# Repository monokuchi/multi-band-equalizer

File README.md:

<!-- PROJECT LOGO -->
<div align="center">
  <h1>Multi-Band Equalizer</h1>
  <p>
    Multi-band parametric equalizer implemented using a STM32H7 ARM7 Microcontroller along with a Cirrus Logic CS4272-CZZ Audio Codec
  </p>
</div>

<!-- PROJECT DESCRIPTION -->
<h2>Description</h2> 

<header>
    <ul>
        <li><h3>Multi-Band-Equalizer Front Side</h3></li>
    </ul>
</header>

![Multi-Band-Equalizer PCB Front Side][multi-band-equalizer-pcb-front]

<header>
    <ul>
        <li><h3>Multi-Band-Equalizer Back Side</h3></li>
    </ul>
</header>

![Multi-Band-Equalizer PCB Back Side][multi-band-equalizer-pcb-back]

<header>
    <ul>
        <li><h3>CS4272-CZZ Breakout Board</h3></li>
    </ul>
</header>

![CS4272-CZZ_Breakout_Board PCB Front Side][cs4272-czz_breakout_board-front]

10-band parametric equalizer using digital 2 stage IIR peaking filters.

Features:
* Efficent pipelining of stereo audio samples to/from the MCU and the codec by utilizing double buffering as well as DMA streams
* Fast computation of cascaded IIR filter stages by taking advantage of ARM's CMSIS DSP libaries (Decreases compute time by ~64%!)
* Generic design of hardware allows for this PCB to used for more then an EQ. All you need to do is change the firmware to alter the processing of the audio samples

Check out this *[script][python-script-url]* for simulating the cascaded filter responses

<p align="right">(<a href="#readme-top">back to top</a>)</p>

<!-- MARKDOWN LINKS & IMAGES -->
[multi-band-equalizer-pcb-front]: pcb/multi-band-equalizer/References/multi-band-equalizer_front.png
[multi-band-equalizer-pcb-back]: pcb/multi-band-equalizer/References/multi-band-equalizer_back.png
[cs4272-czz_breakout_board-front]: pcb/CS4272-CZZ_Breakout_Board/References/CS4272-CZZ_Breakout_Board.png
[python-script-url]: scripts/peaking_filter.py

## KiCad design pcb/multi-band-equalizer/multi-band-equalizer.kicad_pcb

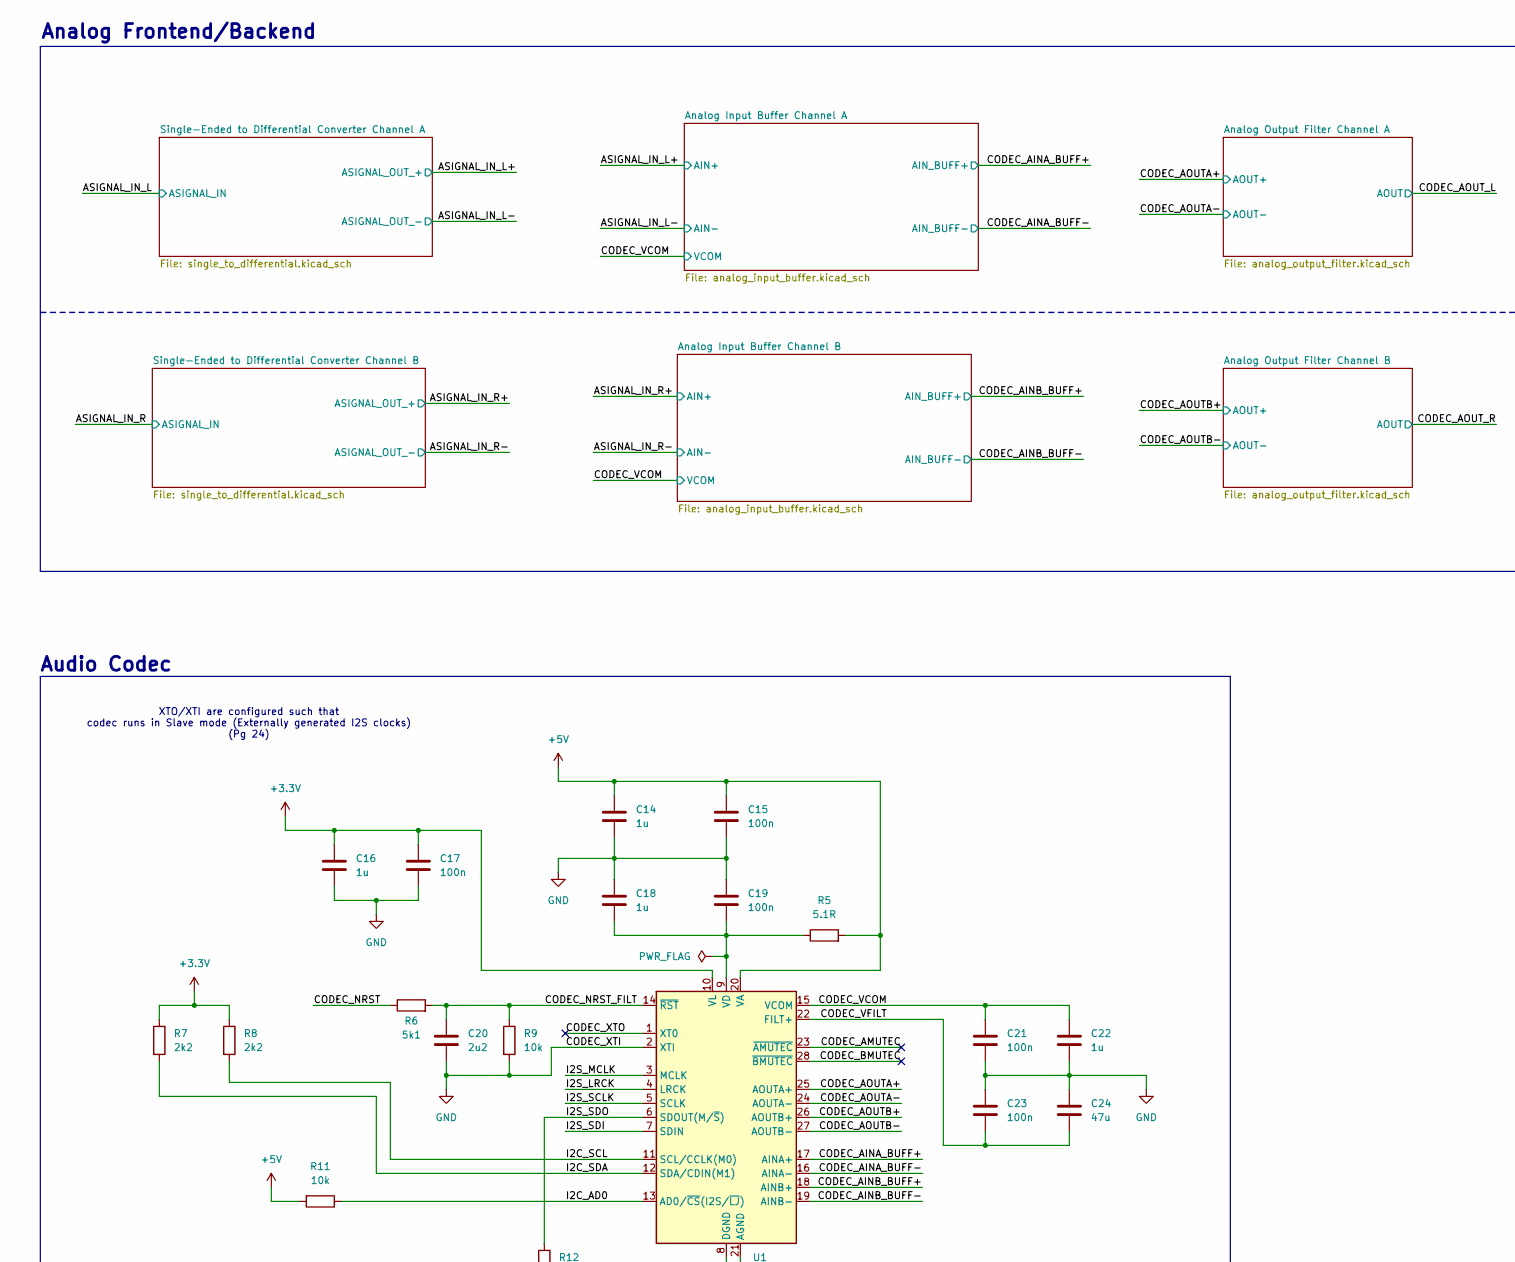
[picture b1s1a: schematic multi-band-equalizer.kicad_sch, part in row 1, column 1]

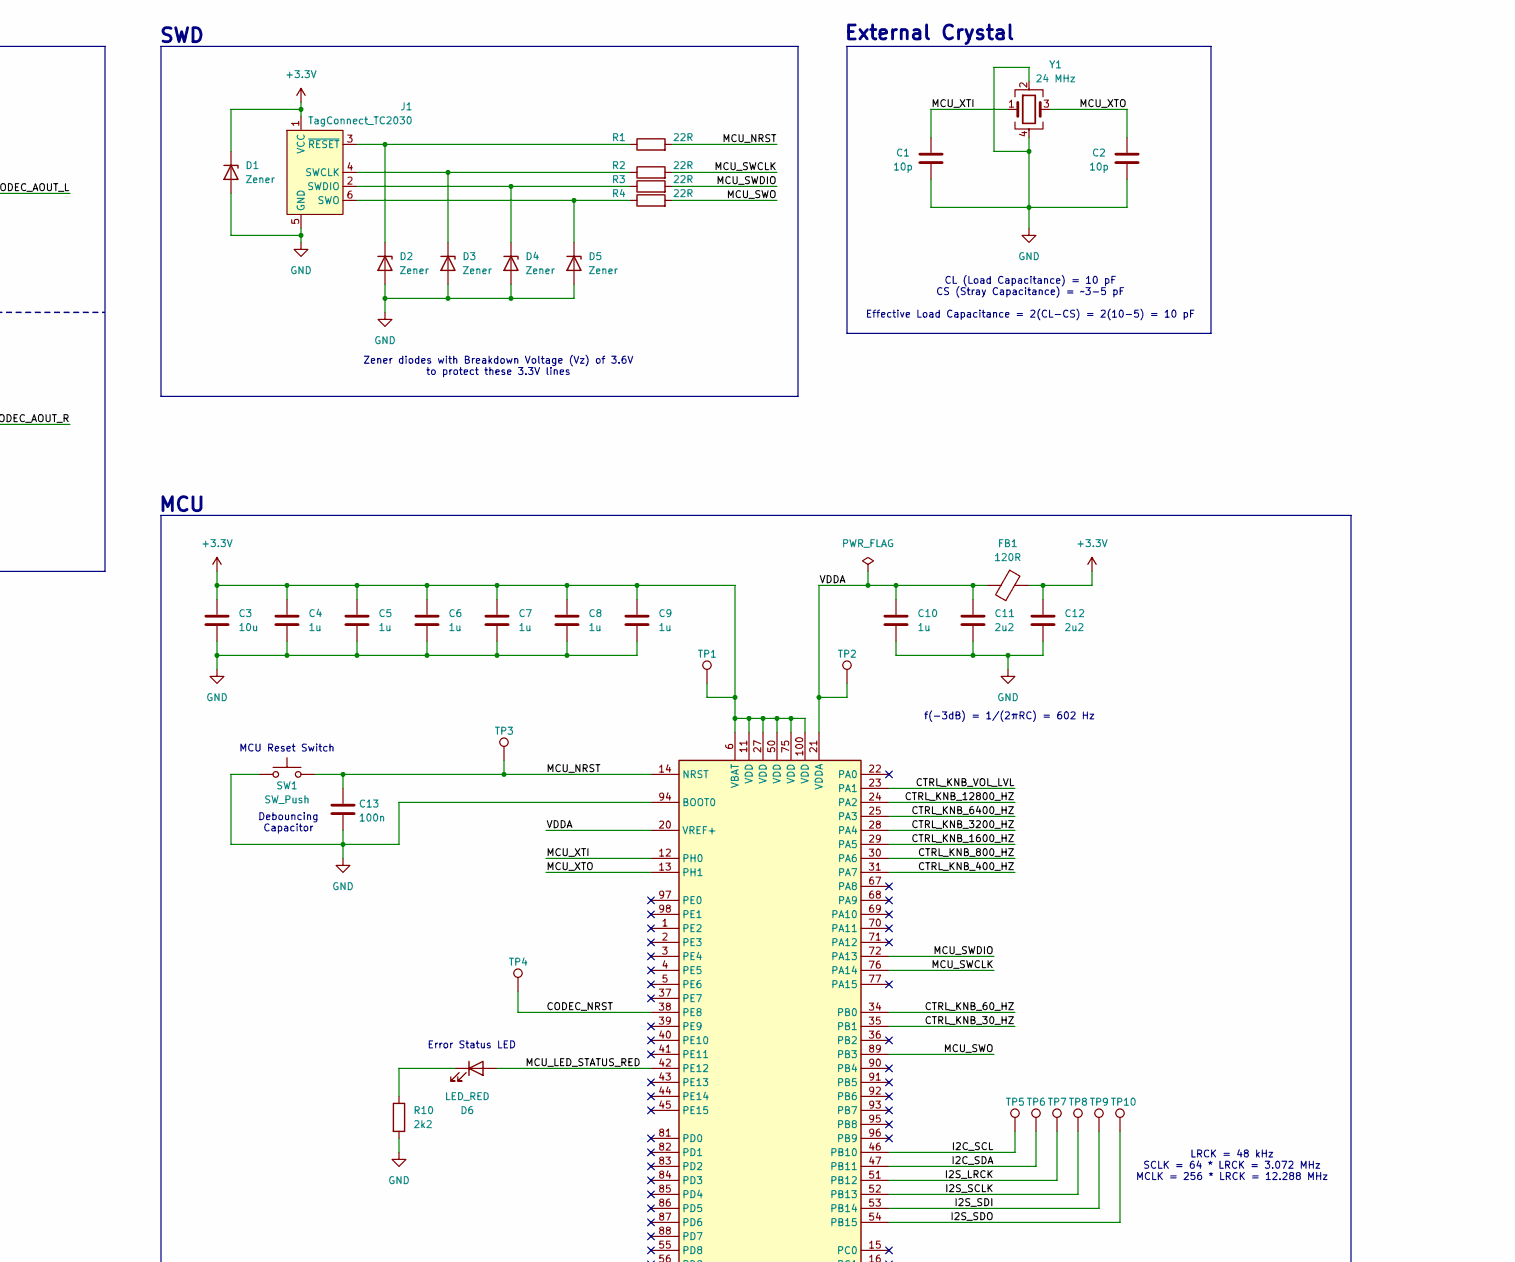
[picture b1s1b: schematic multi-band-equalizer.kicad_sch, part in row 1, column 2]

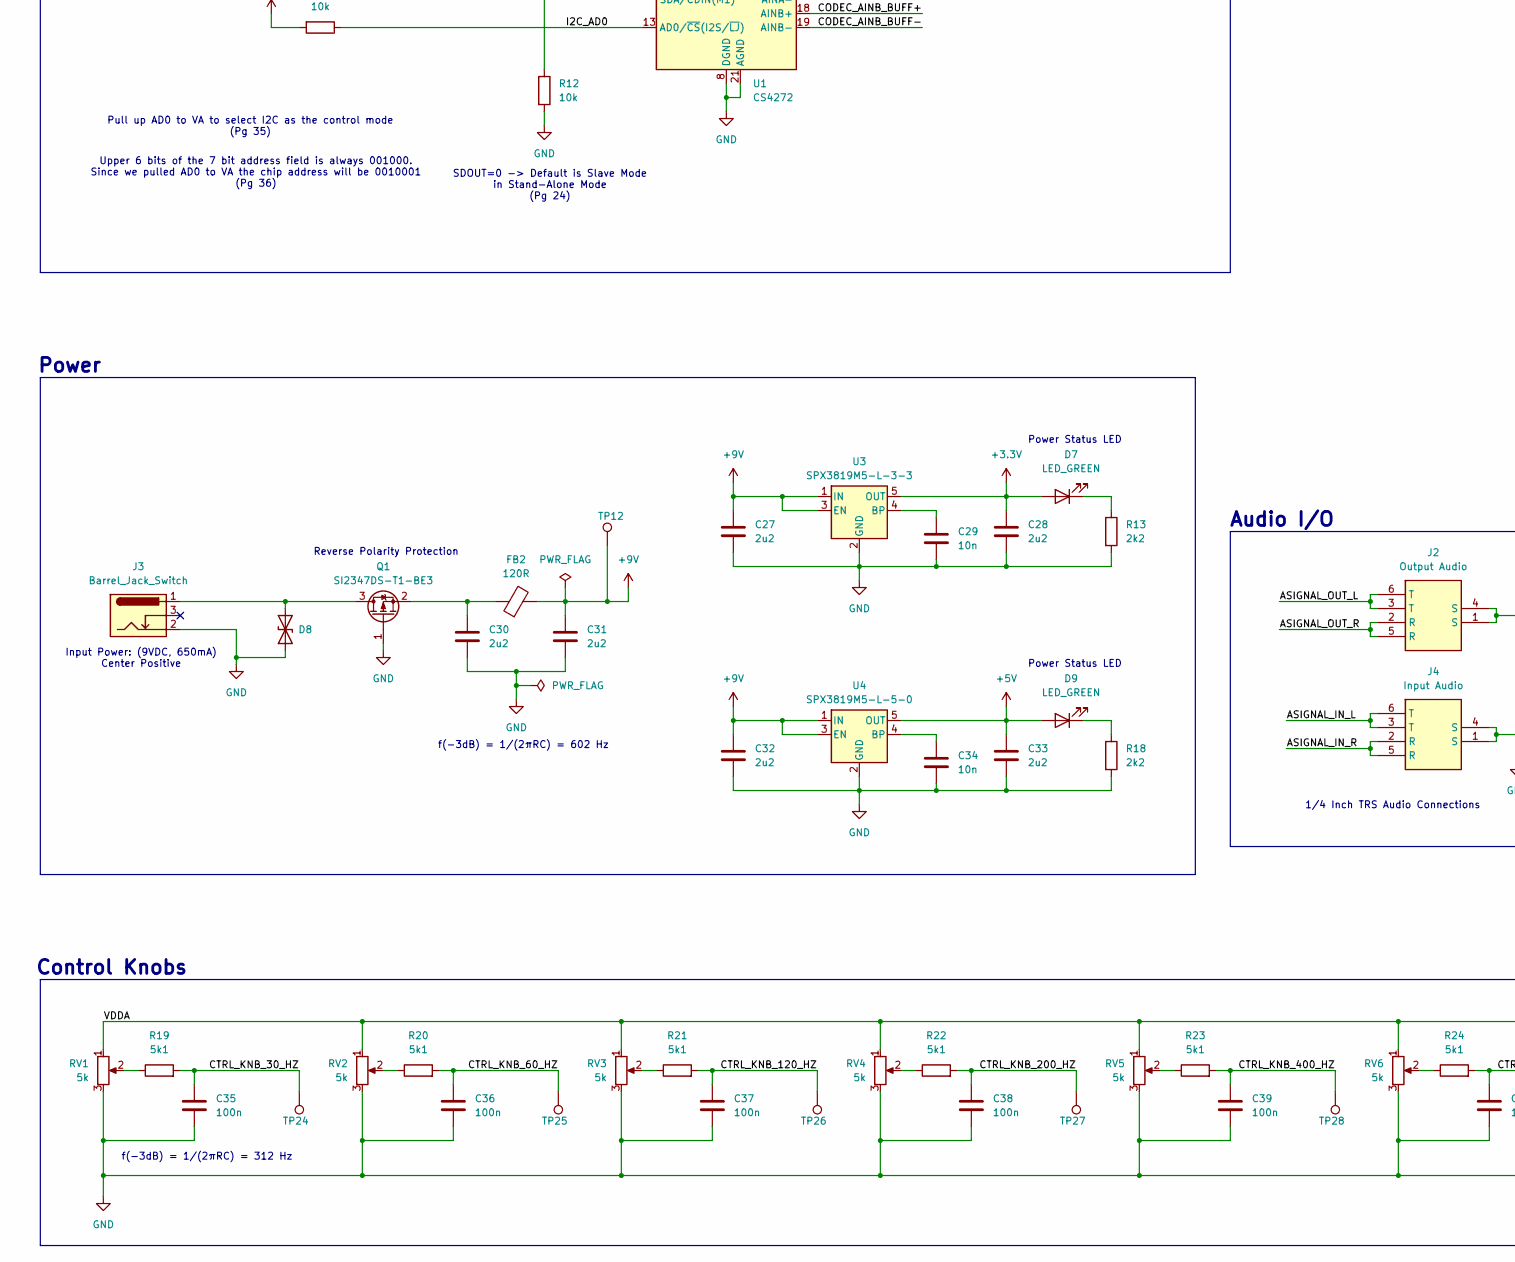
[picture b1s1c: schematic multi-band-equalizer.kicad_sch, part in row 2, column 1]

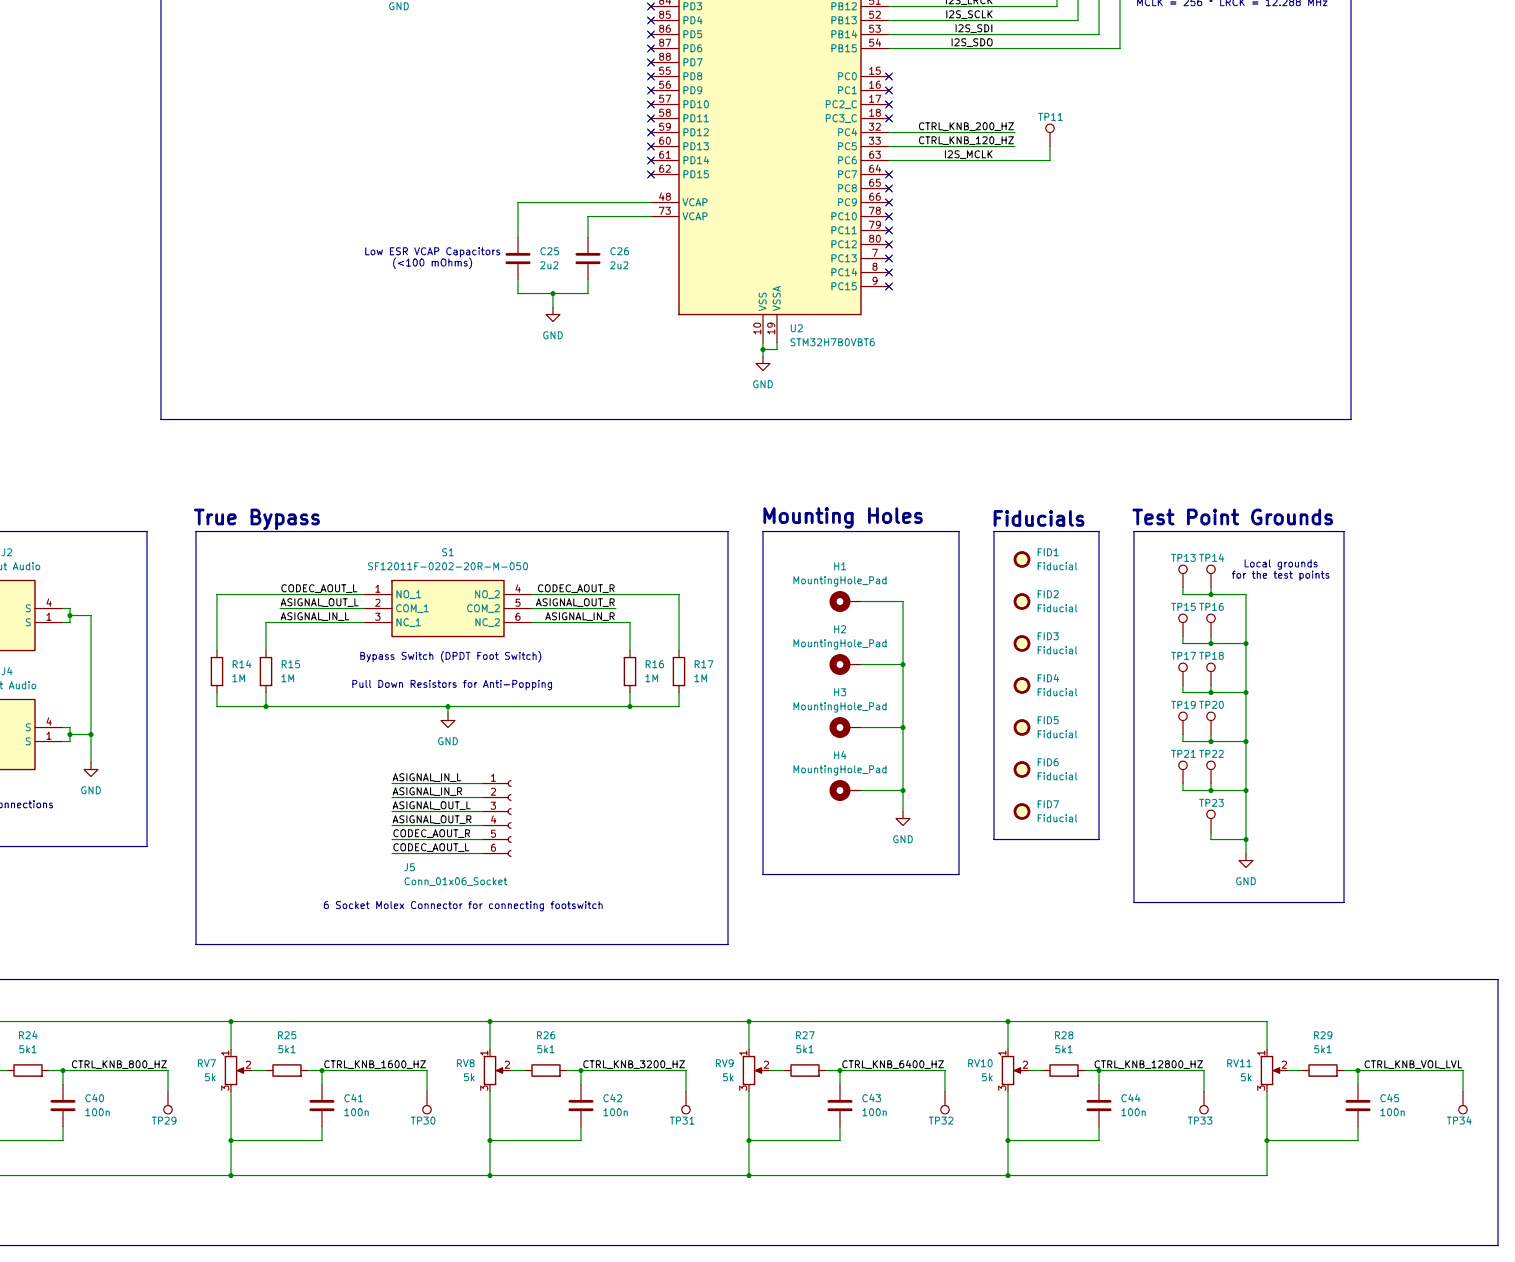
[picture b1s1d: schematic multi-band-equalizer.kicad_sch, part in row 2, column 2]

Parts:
C1, C2: 10p; C_0805_2012Metric
C3: 10u; C_0805_2012Metric
C4, C5, C6, C7, C8, C9, C10, C14, C16, C18, C22: 1u; C_0805_2012Metric
C11, C12, C20, C25, C26, C27, C28, C30, C31, C32, C33: 2u2; C_0805_2012Metric
C13, C15, C17, C19, C21, C23, C35, C36, C37, C38, C39, C40, C41, C42, C43, C44, C45: 100n; C_0805_2012Metric
C24: 47u; C_0805_2012Metric
C29, C34: 10n; C_0805_2012Metric
D1, D2, D3, D4, D5: Zener; D_SOD-323
D6: LED_RED; LED_0805_2012Metric
D7, D9: LED_GREEN; LED_0805_2012Metric
D8: D_TVS; D_SOD-123F
FB1, FB2: 120R; L_0805_2012Metric
FID1, FID2, FID3, FID4, FID5, FID6: Fiducial; Fiducial_1mm_Mask3mm
FID7: Fiducial; Fiducial_1mm_Mask2mm
H1, H2, H3, H4: MountingHole_Pad; MountingHole_4.3mm_M4_Pad_Via
J1: TagConnect_TC2030; Tag-Connect_TC2030-IDC-FP_2x03_P1.27mm_Vertical
J2: Output Audio; ACJSMHDR; Manufacturer_Part_Number ACJS-MHDR; Mouser Part Number 523-ACJS-MHDR
J3: Barrel_Jack_Switch; BarrelJack_Horizontal
J4: Input Audio; ACJSMHDR; Manufacturer_Part_Number ACJS-MHDR; Mouser Part Number 523-ACJS-MHDR
J5: Conn_01x06_Socket; JST_XH_S6B-XH-A_1x06_P2.50mm_Horizontal
Q1: SI2347DS-T1-BE3; SOT-23-3
R1, R2, R3, R4: 22R; R_0805_2012Metric
R5: 5.1R; R_0805_2012Metric
R6, R19, R20, R21, R22, R23, R24, R25, R26, R27, R28, R29: 5k1; R_0805_2012Metric
R7, R8, R10, R13, R18: 2k2; R_0805_2012Metric
R9, R11, R12: 10k; R_0805_2012Metric
R14, R15, R16, R17: 1M; R_0805_2012Metric
RV1, RV2, RV3, RV4, RV5, RV6, RV7, RV8, RV9, RV10, RV11: 5k; PTA2043-2015CPB502
S1: SF12011F-0202-20R-M-050; SF12011F020220RM050; Manufacturer_Part_Number SF12011F-0202-20R-M-050; Mouser Part Number 107-SF12011F-M
SW1: SW_Push; SW_PUSH_6mm_H4.3mm
TP1, TP2, TP3, TP4, TP5, TP6, TP7, TP8, TP9, TP10, TP11, TP12, TP13, TP14, TP15, TP16, TP17, TP18, TP19, TP20, TP21, TP22, TP23, TP24, TP25, TP26, TP27, TP28, TP29, TP30, TP31, TP32, TP33, TP34: TestPoint; TestPoint_THTPad_D1.0mm_Drill0.5mm
U1: CS4272; TSSOP-28_4.4x9.7mm_P0.65mm
U2: STM32H7B0VBT6; LQFP-100_14x14mm_P0.5mm
U3: SPX3819M5-L-3-3; SOT-23-5
U4: SPX3819M5-L-5-0; SOT-23-5
Y1: 24 MHz; Crystal_SMD_2520-4Pin_2.5x2.0mm

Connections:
+3.3V: C3.1, C4.1, C5.1, C6.1, C7.1, C8.1, C9.1, C12.1, C16.1, C17.1, C28.1, D1.1 (K), D7.2 (A), FB1.2, J1.1 (VCC), R7.1, R8.1, TP1.1, U1.10 (VL), U2.6 (VBAT), U2.11 (VDD), U2.27 (VDD), U2.50 (VDD), U2.75 (VDD), U2.100 (VDD), U3.5 (OUT)
+5V: C14.1, C15.1, C33.1, D9.2 (A), R5.2, R11.2, U1.20 (VA), U4.5 (OUT); also elsewhere on the board
+9V: C27.1, C31.1, C32.1, FB2.2, TP12.1, U3.1 (IN), U3.3 (EN), U4.1 (IN), U4.3 (EN)
/ASIGNAL_IN_L: J4.3 (T), J4.6 (T), J5.1, R15.1, S1.3 (NC_1); also elsewhere on the board
/ASIGNAL_IN_R: J4.2 (R), J4.5 (R), J5.2, R16.1, S1.6 (NC_2); also elsewhere on the board
/ASIGNAL_OUT_L: J2.3 (T), J2.6 (T), J5.3, S1.2 (COM_1)
/ASIGNAL_OUT_R: J2.2 (R), J2.5 (R), J5.4, S1.5 (COM_2)
/CODEC_AINA_BUFF+: U1.17 (AINA+); also elsewhere on the board
/CODEC_AINA_BUFF-: U1.16 (AINA-); also elsewhere on the board
/CODEC_AINB_BUFF+: U1.18 (AINB+); also elsewhere on the board
/CODEC_AINB_BUFF-: U1.19 (AINB-); also elsewhere on the board
/CODEC_AMUTEC: U1.23 (~AMUTEC)
/CODEC_AOUTA+: U1.25 (AOUTA+); also elsewhere on the board
/CODEC_AOUTA-: U1.24 (AOUTA-); also elsewhere on the board
/CODEC_AOUTB+: U1.26 (AOUTB+); also elsewhere on the board
/CODEC_AOUTB-: U1.27 (AOUTB-); also elsewhere on the board
/CODEC_AOUT_L: J5.6, R14.1, S1.1 (NO_1); also elsewhere on the board
/CODEC_AOUT_R: J5.5, R17.1, S1.4 (NO_2); also elsewhere on the board
/CODEC_BMUTEC: U1.28 (~BMUTEC)
/CODEC_NRST: R6.1, TP4.1, U2.38 (PE8)
/CODEC_NRST_FILT: C20.1, R6.2, R9.1, U1.14 (~RST)
/CODEC_VCOM: C21.1, C22.1, U1.15 (VCOM); also elsewhere on the board
/CODEC_VFILT: C23.2, C24.2, U1.22 (FILT+)
/CODEC_XTO: U1.1 (XT0)
/CTRL_KNB_30_HZ: C35.1, R19.2, TP24.1, U2.35 (PB1)
/CTRL_KNB_60_HZ: C36.1, R20.2, TP25.1, U2.34 (PB0)
/CTRL_KNB_120_HZ: C37.1, R21.2, TP26.1, U2.33 (PC5)
/CTRL_KNB_200_HZ: C38.1, R22.2, TP27.1, U2.32 (PC4)
/CTRL_KNB_400_HZ: C39.1, R23.2, TP28.1, U2.31 (PA7)
/CTRL_KNB_800_HZ: C40.1, R24.2, TP29.1, U2.30 (PA6)
/CTRL_KNB_1600_HZ: C41.1, R25.2, TP30.1, U2.29 (PA5)
/CTRL_KNB_3200_HZ: C42.1, R26.2, TP31.1, U2.28 (PA4)
/CTRL_KNB_6400_HZ: C43.1, R27.2, TP32.1, U2.25 (PA3)
/CTRL_KNB_12800_HZ: C44.1, R28.2, TP33.1, U2.24 (PA2)
/CTRL_KNB_VOL_LVL: C45.1, R29.2, TP34.1, U2.23 (PA1)
/I2C_AD0: R11.1, U1.13 (AD0/~CS(I2S/~LJ))
/I2C_SCL: R8.2, TP5.1, U1.11 (SCL/CCLK(M0)), U2.46 (PB10)
/I2C_SDA: R7.2, TP6.1, U1.12 (SDA/CDIN(M1)), U2.47 (PB11)
/I2S_LRCK: TP7.1, U1.4 (LRCK), U2.51 (PB12)
/I2S_MCLK: TP11.1, U1.3 (MCLK), U2.63 (PC6)
/I2S_SCLK: TP8.1, U1.5 (SCLK), U2.52 (PB13)
/I2S_SDI: TP9.1, U1.7 (SDIN), U2.53 (PB14)
/I2S_SDO: R12.1, TP10.1, U1.6 (SDOUT(M/~S)), U2.54 (PB15)
/MCU_LED_STATUS_RED: D6.2 (A), U2.42 (PE12)
/MCU_NRST: C13.1, R1.2, SW1.2, TP3.1, U2.14 (NRST)
/MCU_SWCLK: R2.2, U2.76 (PA14)
/MCU_SWDIO: R3.2, U2.72 (PA13)
/MCU_SWO: R4.2, U2.89 (PB3)
/MCU_XTI: C1.1, U2.12 (PH0), Y1.1
/MCU_XTO: C2.1, U2.13 (PH1), Y1.3
/VDDA: C10.1, C11.1, FB1.1, RV1.1, RV2.1, RV3.1, RV4.1, RV5.1, RV6.1, RV7.1, RV8.1, RV9.1, RV10.1, RV11.1, TP2.1, U2.20 (VREF+), U2.21 (VDDA)
GND: C1.2, C2.2, C3.2, C4.2, C5.2, C6.2, C7.2, C8.2, C9.2, C10.2, C11.2, C12.2, C13.2, C14.2, C15.2, C16.2, C17.2, C18.1, C19.1, C20.2, C21.2, C22.2, C23.1, C24.1, C25.2, C26.2, C27.2, C28.2, C29.2, C30.2, C31.2, C32.2, C33.2, C34.2, C35.2, C36.2, C37.2, C38.2, C39.2, C40.2, C41.2, C42.2, C43.2, C44.2, C45.2, D1.2 (A), D2.2 (A), D3.2 (A), D4.2 (A), D5.2 (A), D8.1 (A1), H1.1, H2.1, H3.1, H4.1, J1.5 (GND), J2.1 (S), J2.4 (S), J3.2, J4.1 (S), J4.4 (S), Q1.1 (G), R9.2, R10.2, R12.2, R13.2, R14.2, R15.2, R16.2, R17.2, R18.2, RV1.3, RV2.3, RV3.3, RV4.3, RV5.3, RV6.3, RV7.3, RV8.3, RV9.3, RV10.3, RV11.3, SW1.1, TP13.1, TP14.1, TP15.1, TP16.1, TP17.1, TP18.1, TP19.1, TP20.1, TP21.1, TP22.1, TP23.1, U1.2 (XTI), U1.8 (DGND), U1.21 (AGND), U2.10 (VSS), U2.19 (VSSA), U2.26 (VSS), U2.49 (VSS), U2.74 (VSS), U2.94 (BOOT0), U2.99 (VSS), U3.2 (GND), U4.2 (GND), Y1.2, Y1.4; also elsewhere on the board
unnamed: C25.1, U2.48 (VCAP)
unnamed: C26.1, U2.73 (VCAP)
unnamed: D2.1 (K), J1.3 (~RESET), R1.1
unnamed: D3.1 (K), J1.4 (SWCLK), R2.1
unnamed: D4.1 (K), J1.2 (SWDIO), R3.1
unnamed: D5.1 (K), J1.6 (SWO), R4.1
unnamed: D6.1 (K), R10.1
unnamed: D7.1 (K), R13.1
unnamed: D8.2 (A2), J3.1, Q1.3 (D)
unnamed: D9.1 (K), R18.1
unnamed: C30.1, FB2.1, Q1.2 (S)
unnamed: R19.1, RV1.2
unnamed: R20.1, RV2.2
unnamed: R21.1, RV3.2
unnamed: R22.1, RV4.2
unnamed: R23.1, RV5.2
unnamed: R24.1, RV6.2
unnamed: R25.1, RV7.2
unnamed: R26.1, RV8.2
unnamed: R27.1, RV9.2
unnamed: R28.1, RV10.2
unnamed: R29.1, RV11.2
unnamed: C18.2, C19.2, R5.1, U1.9 (VD)
unnamed: C29.1, U3.4 (BP)
unnamed: C34.1, U4.4 (BP)

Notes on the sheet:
Power Status LED
Test Point Grounds
1/4 Inch TRS Audio Connections
Debouncing Capacitor
Bypass Switch (DPDT Foot Switch)
Reverse Polarity Protection
Audio I/O
Error Status LED
Upper 6 bits of the 7 bit address field is always 001000. Since we pulled AD0 to VA the chip address will be 0010001 (Pg 36)
XTO/XTI are configured such that codec runs in Slave mode (Externally generated I2S clocks) (Pg 24)
f(-3dB) = 1/(2πRC) = 602 Hz
MCU
f(-3dB) = 1/(2πRC) = 312 Hz
SWD
LRCK = 48 kHz SCLK = 64 * LRCK = 3.072 MHz MCLK = 256 * LRCK = 12.288 MHz
6 Socket Molex Connector for connecting footswitch
Audio Codec
Local grounds for the test points
Low ESR VCAP Capacitors (<100 mOhms)
Zener diodes with Breakdown Voltage (Vz) of 3.6V to protect these 3.3V lines
SDOUT=0 -> Default is Slave Mode in Stand-Alone Mode (Pg 24)
Fiducials
True Bypass
External Crystal
CL (Load Capacitance) = 10 pF CS (Stray Capacitance) = ~3-5 pF Effective Load Capacitance = 2(CL-CS) = 2(10-5) = 10 pF
Power
Pull Down Resistors for Anti-Popping
Analog Frontend/Backend
Control Knobs
Input Power: (9VDC, 650mA) Center Positive
Mounting Holes
MCU Reset Switch
Pull up AD0 to VA to select I2C as the control mode (Pg 35)

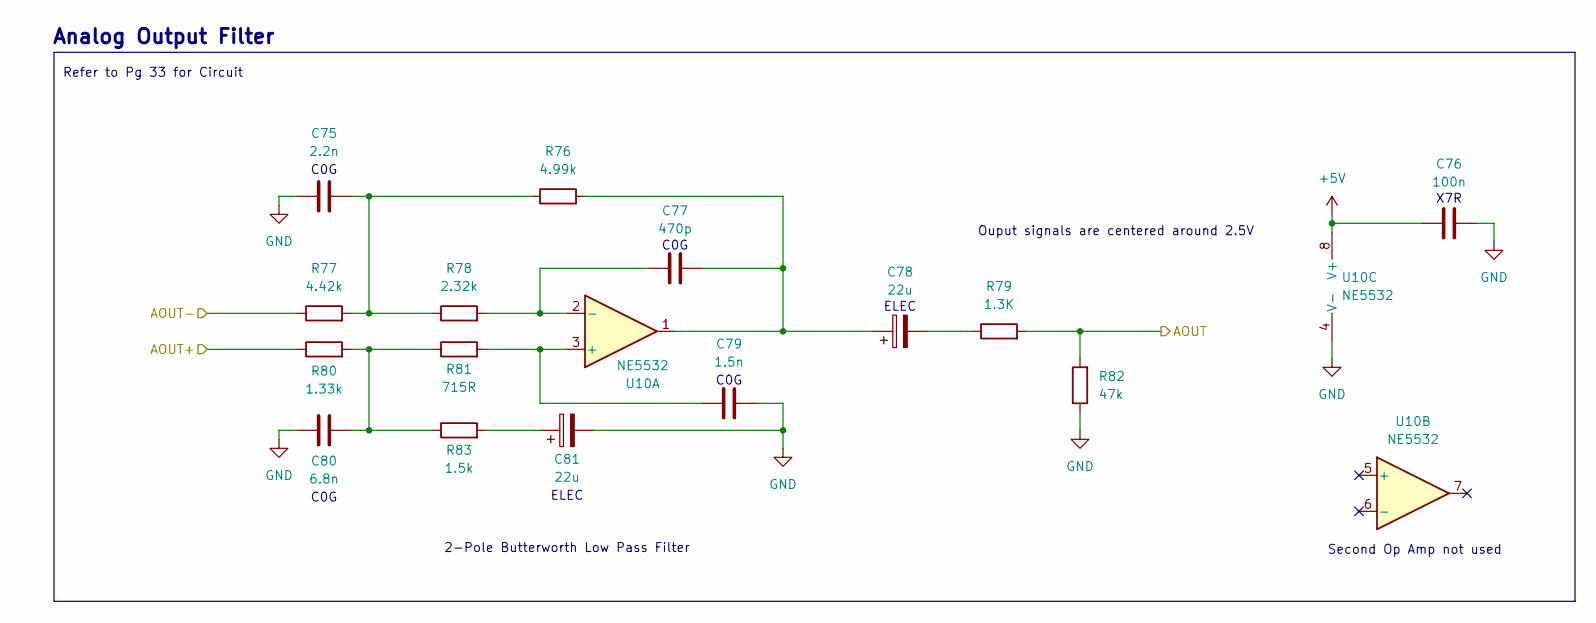
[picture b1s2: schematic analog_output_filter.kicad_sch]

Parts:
C75: 2.2n; C_0805_2012Metric
C76: 100n; C_0805_2012Metric
C77: 470p; C_0805_2012Metric
C78, C81: 22u; CP_Elec_4x5.4
C79: 1.5n; C_0805_2012Metric
C80: 6.8n; C_0805_2012Metric
R76: 4.99k; R_0805_2012Metric
R77: 4.42k; R_0805_2012Metric
R78: 2.32k; R_0805_2012Metric
R79: 1.3K; R_0805_2012Metric
R80: 1.33k; R_0805_2012Metric
R81: 715R; R_0805_2012Metric
R82: 47k; R_0805_2012Metric
R83: 1.5k; R_0805_2012Metric
U10: NE5532; SOIC-8_3.9x4.9mm_P1.27mm

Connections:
+5V: C76.1, U10.8 (V+); also elsewhere on the board
/CODEC_AOUTB+: R80.1; also elsewhere on the board
/CODEC_AOUTB-: R77.1; also elsewhere on the board
/CODEC_AOUT_R: R79.2, R82.2; also elsewhere on the board
GND: C75.1, C76.2, C79.2, C80.1, C81.2, R82.1, U10.4 (V-); also elsewhere on the board
unnamed: C75.2, R76.1, R77.2, R78.1
unnamed: C77.2, C78.1, R76.2, U10.1
unnamed: C78.2, R79.1
unnamed: C80.2, R80.2, R81.1, R83.1
unnamed: C81.1, R83.2
unnamed: C79.1, R81.2, U10.3 (+)
unnamed: C77.1, R78.2, U10.2 (-)

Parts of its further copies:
C68: 2.2n; C_0805_2012Metric
C69: 100n; C_0805_2012Metric
C70: 470p; C_0805_2012Metric
C71, C74: 22u; CP_Elec_4x5.4
C72: 1.5n; C_0805_2012Metric
C73: 6.8n; C_0805_2012Metric
R68: 4.99k; R_0805_2012Metric
R69: 4.42k; R_0805_2012Metric
R70: 2.32k; R_0805_2012Metric
R71: 1.3K; R_0805_2012Metric
R72: 1.33k; R_0805_2012Metric
R73: 715R; R_0805_2012Metric
R74: 47k; R_0805_2012Metric
R75: 1.5k; R_0805_2012Metric
U9: NE5532; SOIC-8_3.9x4.9mm_P1.27mm

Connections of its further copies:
+5V: C69.1, U9.8 (V+); also elsewhere on the board
/CODEC_AOUTA+: R72.1; also elsewhere on the board
/CODEC_AOUTA-: R69.1; also elsewhere on the board
/CODEC_AOUT_L: R71.2, R74.2; also elsewhere on the board
GND: C68.1, C69.2, C72.2, C73.1, C74.2, R74.1, U9.4 (V-); also elsewhere on the board
unnamed: C68.2, R68.1, R69.2, R70.1
unnamed: C70.2, C71.1, R68.2, U9.1
unnamed: C71.2, R71.1
unnamed: C73.2, R72.2, R73.1, R75.1
unnamed: C74.1, R75.2
unnamed: C72.1, R73.2, U9.3 (+)
unnamed: C70.1, R70.2, U9.2 (-)

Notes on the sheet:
C0G
Refer to Pg 33 for Circuit
X7R
2-Pole Butterworth Low Pass Filter
Second Op Amp not used
Ouput signals are centered around 2.5V
ELEC
Analog Output Filter

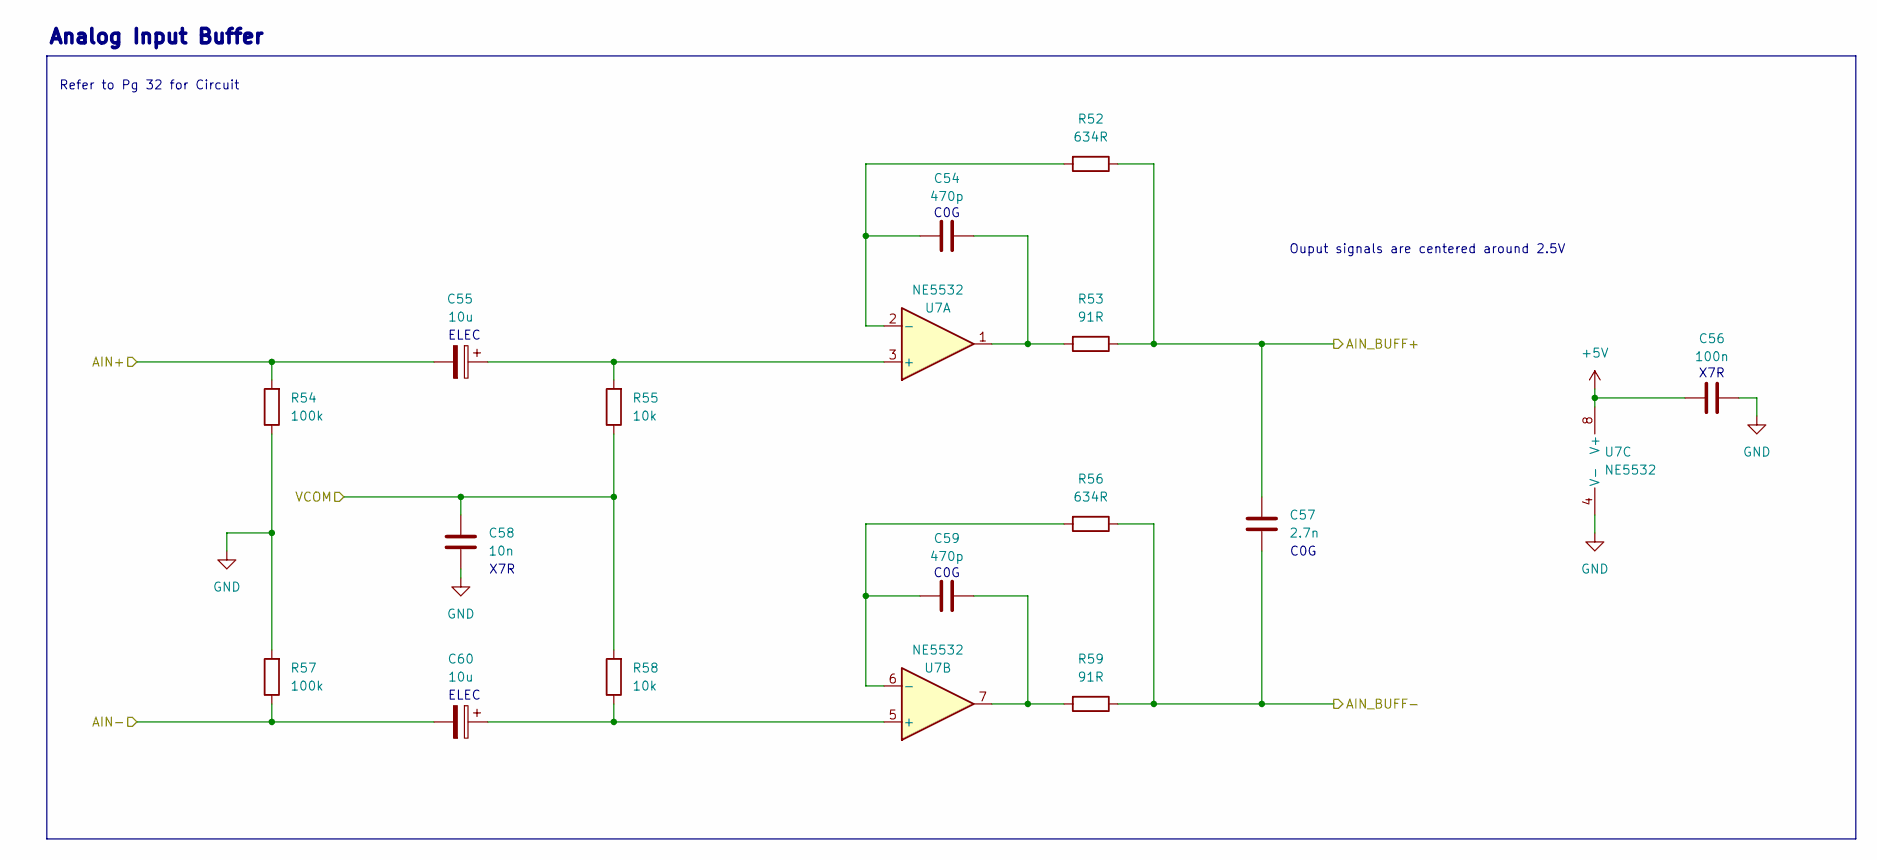
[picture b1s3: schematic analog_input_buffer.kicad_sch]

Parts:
C54, C59: 470p; C_0805_2012Metric
C55, C60: 10u; CP_Elec_5x5.4
C56: 100n; C_0805_2012Metric
C57: 2.7n; C_0805_2012Metric
C58: 10n; C_0805_2012Metric
R52, R56: 634R; R_0805_2012Metric
R53, R59: 91R; R_0805_2012Metric
R54, R57: 100k; R_0805_2012Metric
R55, R58: 10k; R_0805_2012Metric
U7: NE5532; SOIC-8_3.9x4.9mm_P1.27mm

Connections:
+5V: C56.1, U7.8 (V+); also elsewhere on the board
/ASIGNAL_IN_L+: C55.2, R54.2; also elsewhere on the board
/ASIGNAL_IN_L-: C60.2, R57.1; also elsewhere on the board
/CODEC_AINA_BUFF+: C57.2, R52.1, R53.1; also elsewhere on the board
/CODEC_AINA_BUFF-: C57.1, R56.1, R59.1; also elsewhere on the board
/CODEC_VCOM: C58.1, R55.1, R58.2; also elsewhere on the board
GND: C56.2, C58.2, R54.1, R57.2, U7.4 (V-); also elsewhere on the board
unnamed: C54.2, R53.2, U7.1
unnamed: C59.2, R59.2, U7.7
unnamed: C55.1, R55.2, U7.3 (+)
unnamed: C54.1, R52.2, U7.2 (-)
unnamed: C60.1, R58.1, U7.5 (+)
unnamed: C59.1, R56.2, U7.6 (-)

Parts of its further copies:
C61, C66: 470p; C_0805_2012Metric
C62, C67: 10u; CP_Elec_5x5.4
C63: 100n; C_0805_2012Metric
C64: 2.7n; C_0805_2012Metric
C65: 10n; C_0805_2012Metric
R60, R64: 634R; R_0805_2012Metric
R61, R67: 91R; R_0805_2012Metric
R62, R65: 100k; R_0805_2012Metric
R63, R66: 10k; R_0805_2012Metric
U8: NE5532; SOIC-8_3.9x4.9mm_P1.27mm

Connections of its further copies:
+5V: C63.1, U8.8 (V+); also elsewhere on the board
/ASIGNAL_IN_R+: C62.2, R62.2; also elsewhere on the board
/ASIGNAL_IN_R-: C67.2, R65.1; also elsewhere on the board
/CODEC_AINB_BUFF+: C64.2, R60.1, R61.1; also elsewhere on the board
/CODEC_AINB_BUFF-: C64.1, R64.1, R67.1; also elsewhere on the board
/CODEC_VCOM: C65.1, R63.1, R66.2; also elsewhere on the board
GND: C63.2, C65.2, R62.1, R65.2, U8.4 (V-); also elsewhere on the board
unnamed: C61.2, R61.2, U8.1
unnamed: C66.2, R67.2, U8.7
unnamed: C62.1, R63.2, U8.3 (+)
unnamed: C61.1, R60.2, U8.2 (-)
unnamed: C67.1, R66.1, U8.5 (+)
unnamed: C66.1, R64.2, U8.6 (-)

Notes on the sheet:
C0G
Analog Input Buffer
X7R
Refer to Pg 32 for Circuit
Ouput signals are centered around 2.5V
ELEC

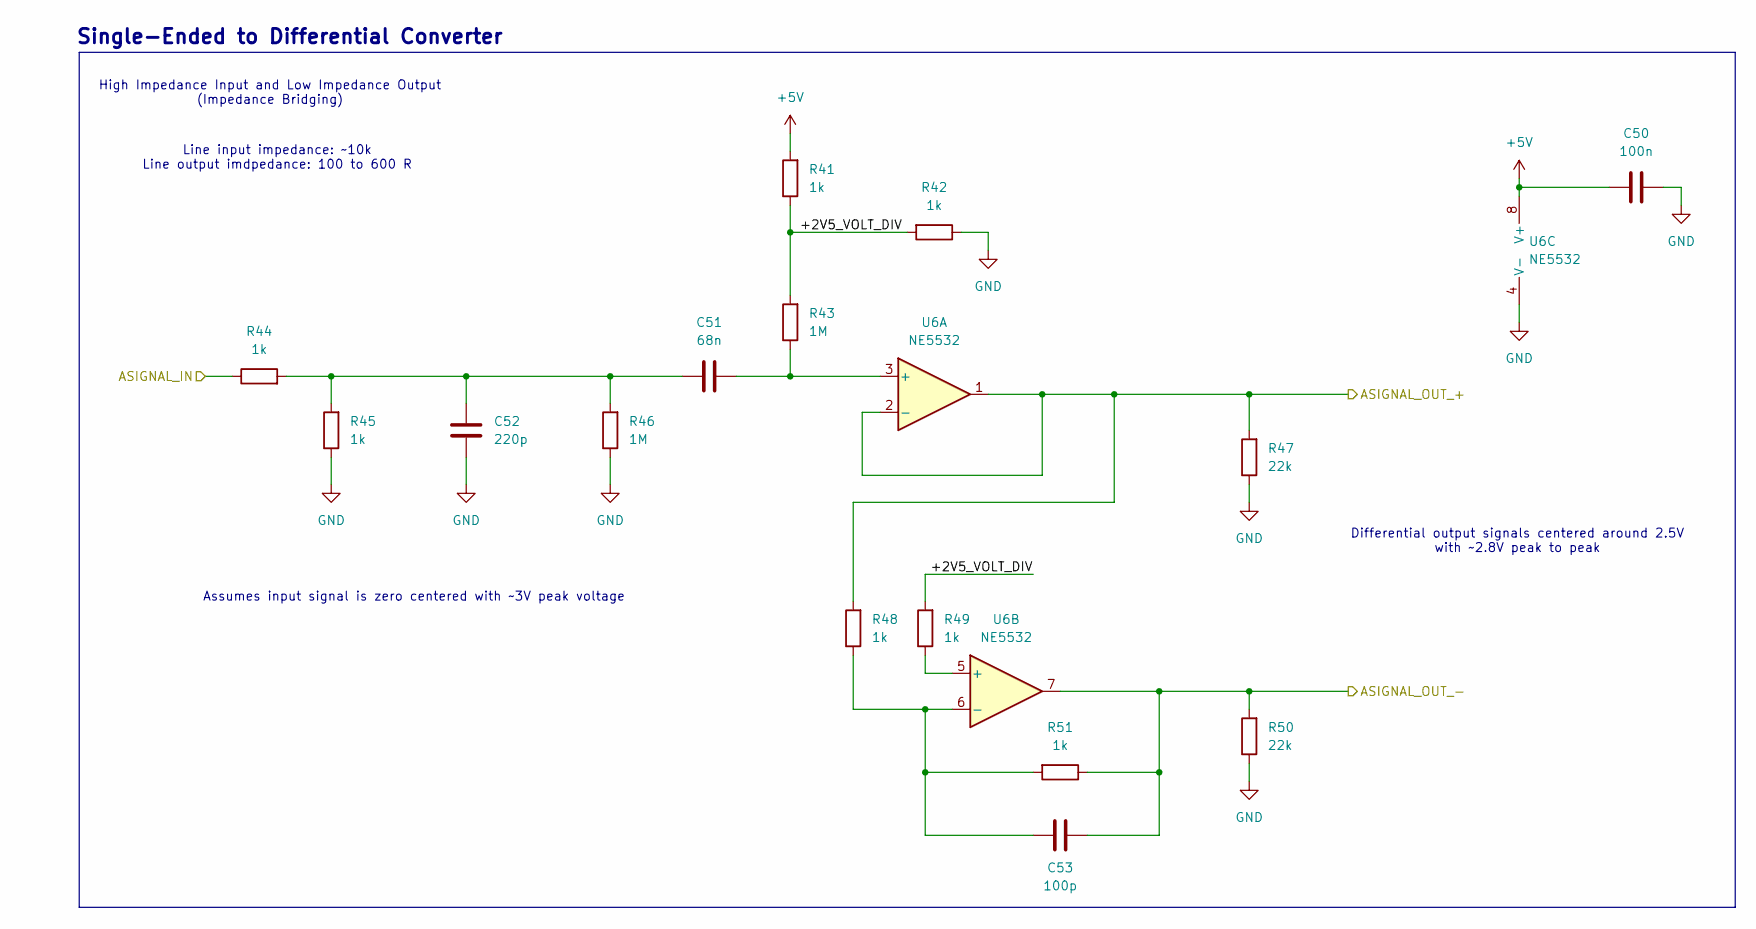
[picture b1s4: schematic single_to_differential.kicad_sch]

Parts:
C50: 100n; C_0805_2012Metric
C51: 68n; C_0805_2012Metric
C52: 220p; C_0805_2012Metric
C53: 100p; C_0805_2012Metric
R41, R42, R44, R45, R48, R49, R51: 1k; R_0805_2012Metric
R43, R46: 1M; R_0805_2012Metric
R47, R50: 22k; R_0805_2012Metric
U6: NE5532; SOIC-8_3.9x4.9mm_P1.27mm

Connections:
+5V: C50.1, R41.2, U6.8 (V+); also elsewhere on the board
/ASIGNAL_IN_R: R44.1; also elsewhere on the board
/ASIGNAL_IN_R+: R47.2, R48.2, U6.1, U6.2 (-); also elsewhere on the board
/ASIGNAL_IN_R-: C53.1, R50.2, R51.1, U6.7; also elsewhere on the board
/Single-Ended to Differential Converter Channel B/+2V5_VOLT_DIV: R41.1, R42.2, R43.2, R49.2
GND: C50.2, C52.2, R42.1, R45.1, R46.1, R47.1, R50.1, U6.4 (V-); also elsewhere on the board
unnamed: C51.1, C52.1, R44.2, R45.2, R46.2
unnamed: C51.2, R43.1, U6.3 (+)
unnamed: R49.1, U6.5 (+)
unnamed: C53.2, R48.1, R51.2, U6.6 (-)

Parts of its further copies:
C46: 100n; C_0805_2012Metric
C47: 68n; C_0805_2012Metric
C48: 220p; C_0805_2012Metric
C49: 100p; C_0805_2012Metric
R30, R31, R33, R34, R37, R38, R40: 1k; R_0805_2012Metric
R32, R35: 1M; R_0805_2012Metric
R36, R39: 22k; R_0805_2012Metric
U5: NE5532; SOIC-8_3.9x4.9mm_P1.27mm

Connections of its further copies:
+5V: C46.1, R30.2, U5.8 (V+); also elsewhere on the board
/ASIGNAL_IN_L: R33.1; also elsewhere on the board
/ASIGNAL_IN_L+: R36.2, R37.2, U5.1, U5.2 (-); also elsewhere on the board
/ASIGNAL_IN_L-: C49.1, R39.2, R40.1, U5.7; also elsewhere on the board
/Single-Ended to Differential Converter Channel A/+2V5_VOLT_DIV: R30.1, R31.2, R32.2, R38.2
GND: C46.2, C48.2, R31.1, R34.1, R35.1, R36.1, R39.1, U5.4 (V-); also elsewhere on the board
unnamed: C47.1, C48.1, R33.2, R34.2, R35.2
unnamed: C47.2, R32.1, U5.3 (+)
unnamed: R38.1, U5.5 (+)
unnamed: C49.2, R37.1, R40.2, U5.6 (-)

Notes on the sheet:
Assumes input signal is zero centered with ~3V peak voltage
Single-Ended to Differential Converter
High Impedance Input and Low Impedance Output (Impedance Bridging)
Differential output signals centered around 2.5V with ~2.8V peak to peak
Line input impedance: ~10k Line output imdpedance: 100 to 600 R

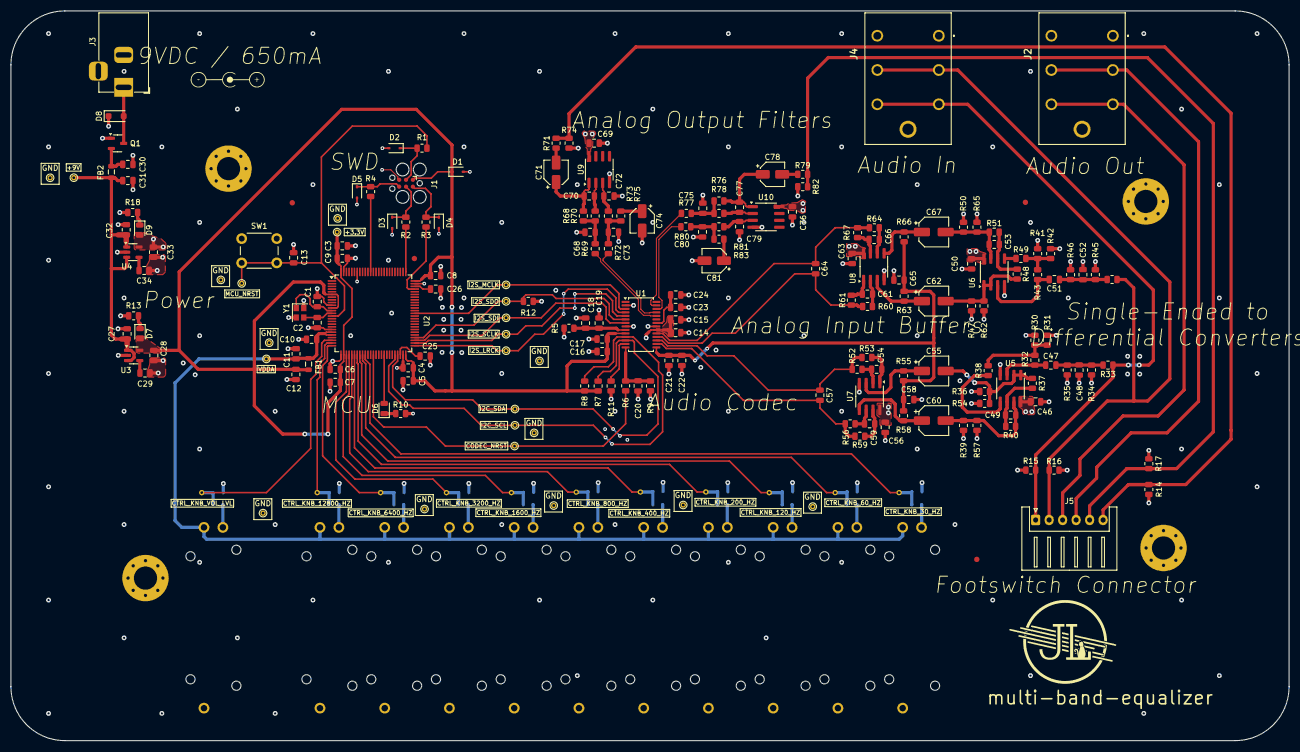
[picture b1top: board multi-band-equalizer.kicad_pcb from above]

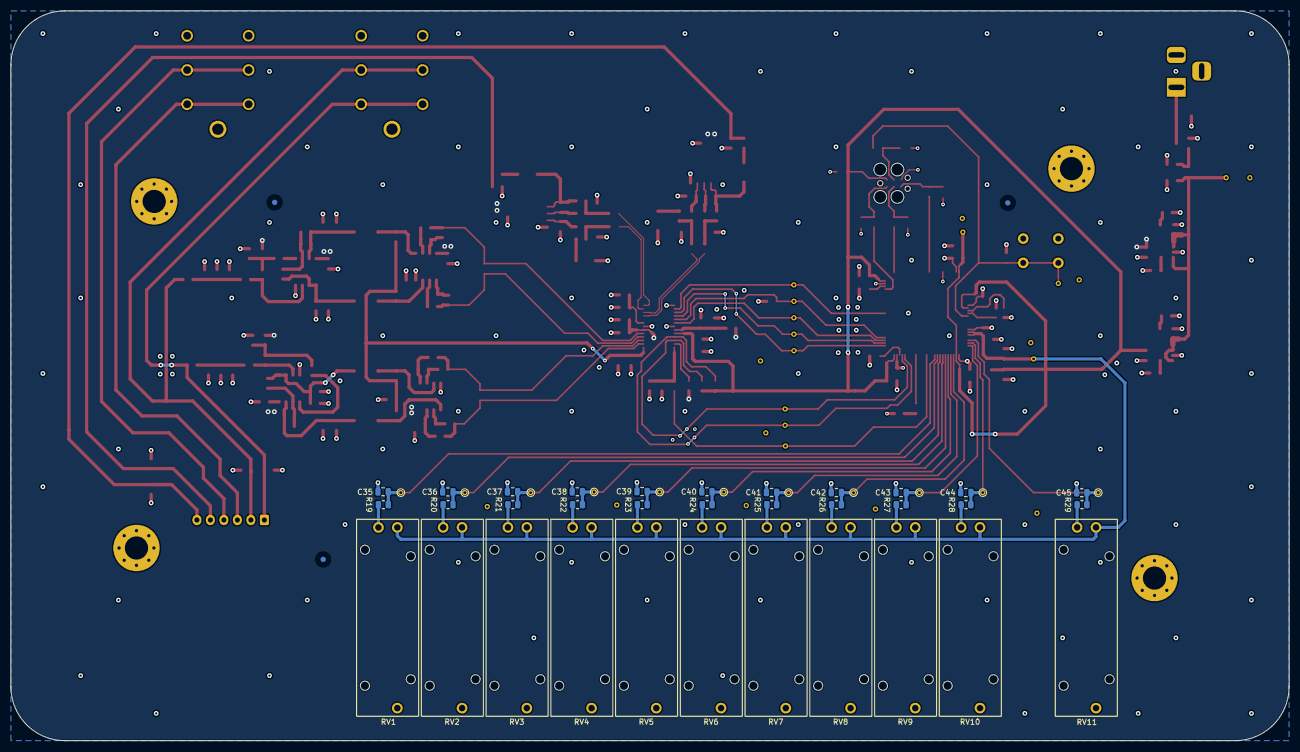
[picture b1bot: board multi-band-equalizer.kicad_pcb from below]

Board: 4 copper layers, 236.9 x 135.2 mm, 249 parts (47 on the bottom side), 114 nets.
